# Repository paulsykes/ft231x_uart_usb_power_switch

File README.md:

FT231X UART USB Power Switch
================================

FT231X USB to serial UART with integrated current limited USB power switch.

It also allows you to switch on and off power to a USB powered device. This is super useful if you are debugging the serial output of a device during hard reset conditions and wish to automate the reset process, even more so if the device you are trying to monitor is connected to a remote computer.

- USB to UART
- USB power output switched by FT231X CBUS0 pin
- Active low, over current status readable by FT231X CBUS3 pin (500 mA)
- Solder jumper to default USB power to on or off
- USB data lines are connected to the FT231X, they are *NOT* passed through to the power switchable USB Type A port. 

Documentation
-------------
Compiled documentation can be read [here](https://paulsykes.me/ft231x_uart_usb_power_switch). Documentation source and build instructions [here](docsrc).

Manufacturing & Releases
------------------------
Fabrication outputs (Gerbers/BoM/etc..) are automatically generated for each release, the latest of which can be found [here](https://github.com/paulsykes/ft231x_uart_usb_power_switch/releases/latest). Instructions for locally generating manufacturing outputs can be found [here](hardware/kicad/ft231x_uart_usb_power_switch).

License Information
-------------------
All contents of this repository are released under [Creative Commons Share-alike 4.0](http://creativecommons.org/licenses/by-sa/4.0/).

Author
------
Paul Sykes, [My Blog](https://paulsykes.me)

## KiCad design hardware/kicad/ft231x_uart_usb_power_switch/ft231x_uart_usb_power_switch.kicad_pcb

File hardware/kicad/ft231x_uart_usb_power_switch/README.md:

Fabrication
===========
The fabrication outputs (Gebers/BoM/etc..) for this project are built using
[KiBot](https://github.com/INTI-CMNB/KiBot). The outputs are automatically generated for each release, the latest of which can be found [here](https://github.com/paulsykes/ft231x_breakout_usb_power_switch/releases/latest).This document will cover generating manufacturing outputs locally.

Build Environment
-----------------
KiBot installation on Ubuntu/Debian. For other OS, please see [KiBot Documentation](https://github.com/skorokithakis/KiBot/blob/master/README.md).
```
$ wget https://github.com/INTI-CMNB/KiBot/releases/download/v0.10.0-4/kibot_0.10.0-4_all.deb
$ sudo apt install ./kibot_0.10.0-4_all.deb
```
KiBot installation on Ubuntu/Debian.
```
$ wget https://github.com/INTI-CMNB/KiAuto/releases/download/v1.5.8/kiauto_1.5.8-1_all.deb
$ sudo apt install ./kiauto_1.5.8-1_all.deb
```
InteractiveHtmlBom installation Ubuntu/Debian.
```
$ wget https://github.com/INTI-CMNB/InteractiveHtmlBom/releases/download/v2.3.4-2/interactivehtmlbom.inti-cmnb_2.3.4-2_all.deb
$ sudo apt install ./interactivehtmlbom.inti-cmnb_2.3.4-2_all.deb
```

Generate Fabrication Outputs
----------------------------
Fabrication outputs will generated inside the [fabrication](fabrication) folder.
``` 
$ cd hardware/kicad/ft231x_breakout_usb_power_switch
$ make
```

Delete Fabrication Outputs
----------------------------
Delete all fabrication outputs.
``` 
$ make clean
```

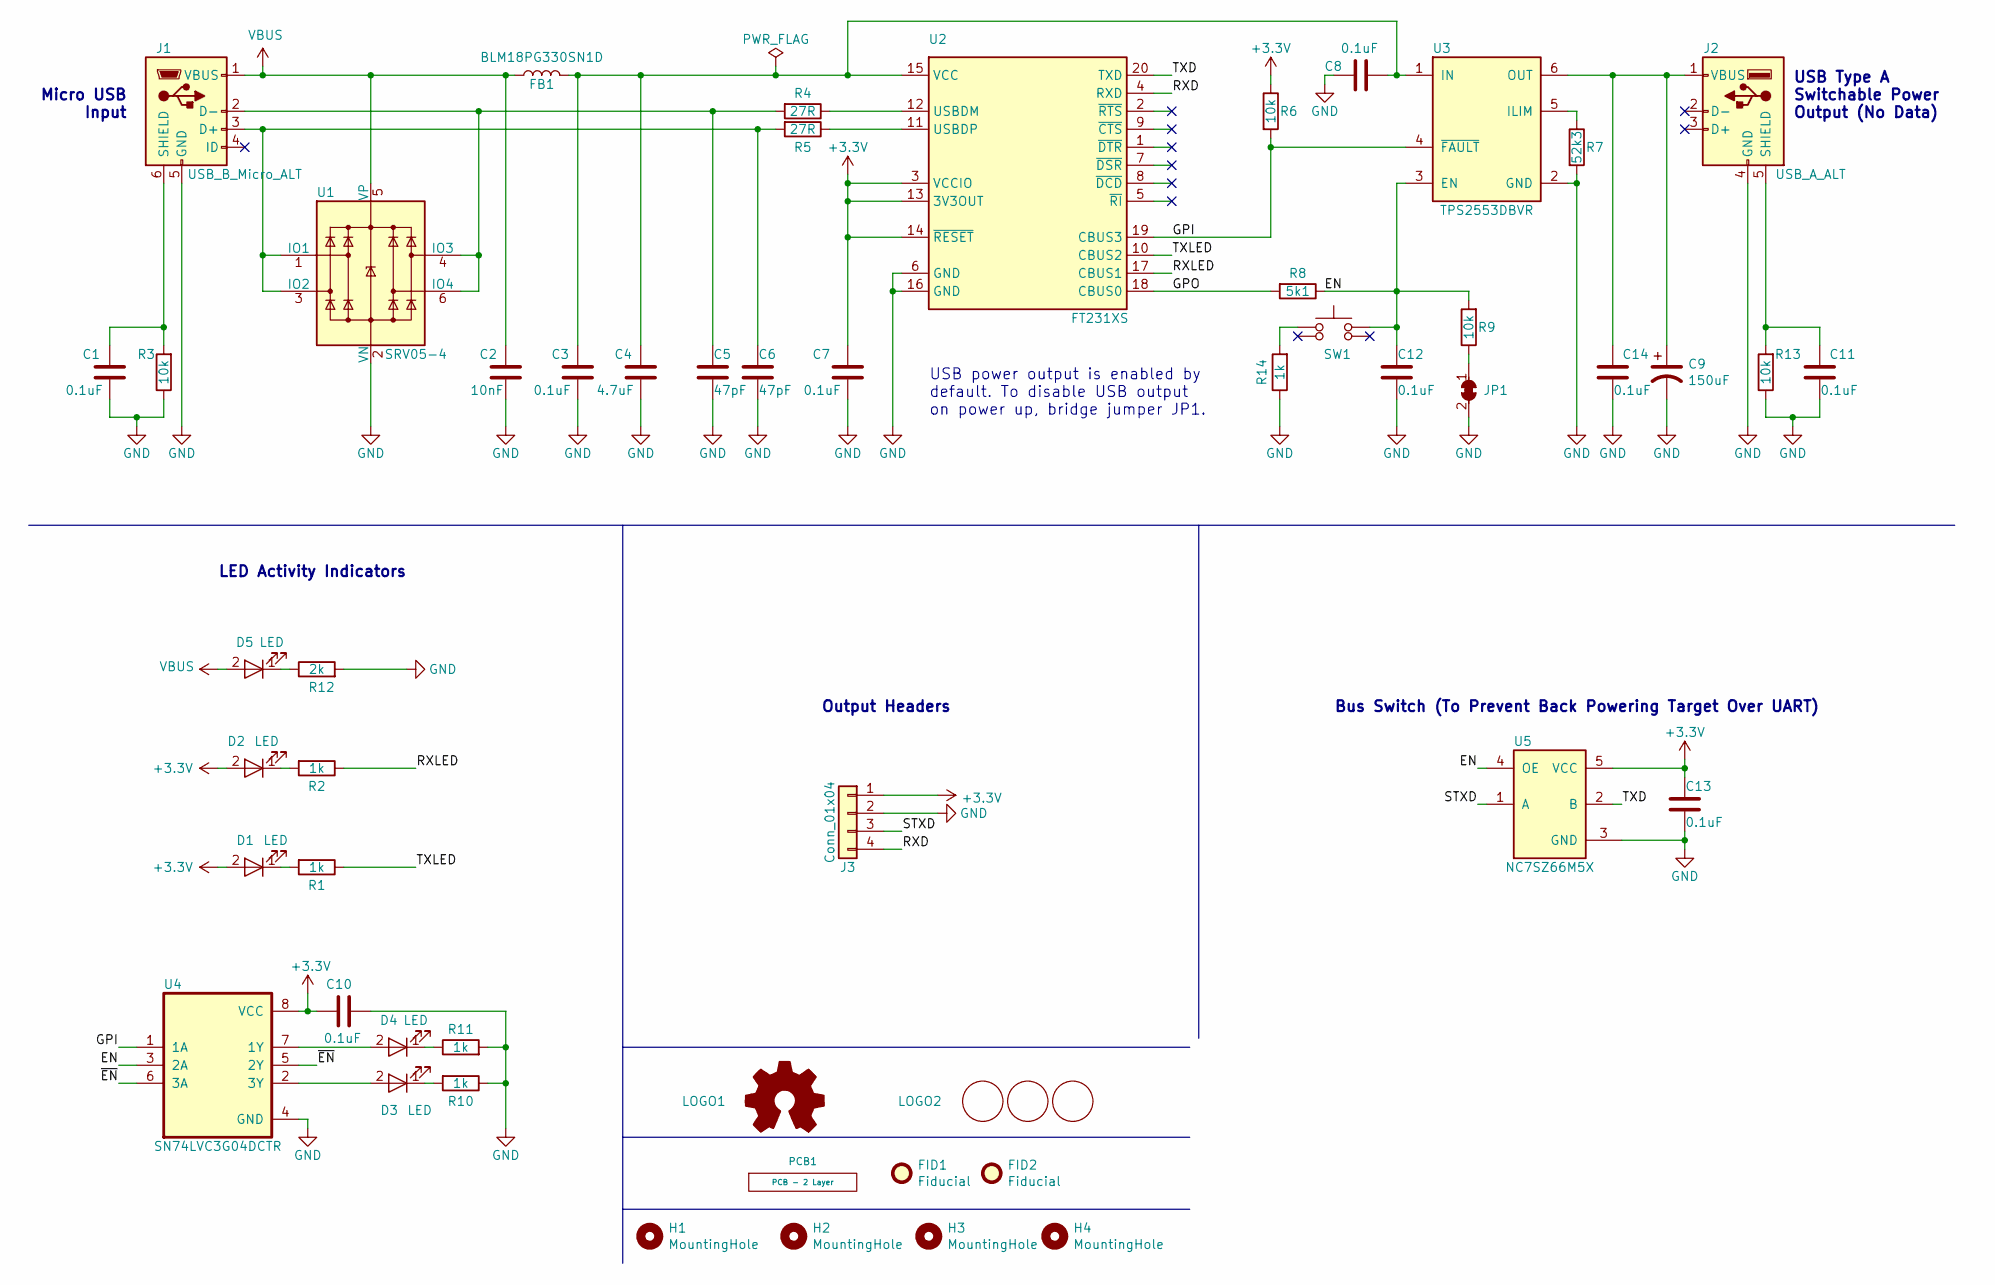
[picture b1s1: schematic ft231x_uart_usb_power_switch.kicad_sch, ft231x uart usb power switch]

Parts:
C1, C3, C7, C8, C10, C11, C12, C13, C14: 0.1uF; C_0603; mouser# 603-CC603KRX7R9BB104; LCSC# C14663
C2: 10nF; C_0603; mouser# 603-CC603KRX7R9BB103; LCSC# C100042
C4: 4.7uF; C_0603; mouser# 603-CC603KRX5R6BB475; LCSC# C109456
C5, C6: 47pF; C_0603; mouser# 603-CC603JRNPO9BN470; LCSC# C105622
C9: 150uF; EIA-3528-12_Kemet-T_DENSITY_MEDIUM; mouser# 80-T520B157M006ATE25; LCSC# C156458
D1, D2, D3, D4, D5: LED; LED_0603_1608Metric; mouser# 638-19217GHCYR1S23T; LCSC# C72043
FB1: BLM18PG330SN1D; FB_0603; mouser# 81-BLM18PG330SN1D; LCSC# C88984
FID1, FID2: Fiducial; Fiducial_1mm_Mask2mm
H1, H3: MountingHole; MountingHole_2.6mm_annular
H2, H4: MountingHole; MountingHole_2.6mm_nocrtyd
J1: USB_B_Micro_ALT; AMPHENOL_10118194-0001LF; mouser# 649-10118194-0001LF; LCSC# C132563
J2: USB_A_ALT; TE_292303-1; mouser# 571-292303-1; LCSC# C86461
J3: Conn_01x04; PinHeader_1x04_P2.54mm_Vertical_Arduino; LCSC# C124378
JP1: SolderJumper_2_Bridged_Alt; SolderJumper-2_P1.3mm_Un-Bridged_RoundedPad1.0x1.5mm
LOGO1: Logo_Open_Hardware_Small; OSHW-Logo2_7.3x6mm_SilkScreen
LOGO2: Logo_CC_BY_SA; cc_by_sa
PCB1: PCB - 2 Layer
R1, R2, R10, R11, R14: 1k; R_0603; mouser# 603-RC0603JR-071KL; LCSC# C14676
R3, R6, R9, R13: 10k; R_0603; mouser# 603-RC0603JR-0710KL; LCSC# C99198
R4, R5: 27R; R_0603; mouser# 603-RC0603FR-0727RL; LCSC# C137753
R7: 52k3; R_0603; mouser# 603-RC0603FR-0752K3L; LCSC# C185323
R8: 5k1; R_0603; mouser# 603-RC0603JR-075K1L; LCSC# C14677
R12: 2k; R_0603; mouser# 603-RC0603JR-072KL; LCSC# C105581
SW1: PTS810SJK250SMTRLFS; PTS810SJK250SMTRLFS-TACT4.2MM; mouser# 611-PTS810SJK250SMTR; LCSC# C221896
U1: SRV05-4; SOT-23-6; LCSC# C558418
U2: FT231XS; SSOP-20_3.9x8.7mm_P0.635mm; mouser# 895-FT231XS-R; LCSC# C132160
U3: TPS2553DBVR; VSON-10-1EP_3x3mm_P0.5mm_EP1.65x2.4mm_ThermalVias; mouser# 595-TPS2553DBVR; LCSC# C55266
U4: SN74LVC3G04DCTR; SSOP-8_2.95x2.8mm_P0.65mm; mouser# 595-SN74LVC3G04DCTR; LCSC# C139324
U5: NC7SZ66M5X; SOT-23-5; mouser# 512-NC7SZ66M5X; LCSC# C232791

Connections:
+3V3: C7.1, C10.1, C13.1, D1.2 (A), D2.2 (A), J3.1, R6.1, U2.3 (VCCIO), U2.13 (3V3OUT), U2.14 (~RESET), U4.8 (VCC), U5.5 (VCC)
/EN: C12.1, R8.1, R9.2, SW1.3 (B), U3.3 (EN), U4.3 (2A), U5.4 (OE)
/GPI: R6.2, U2.19 (CBUS3), U3.4 (~FAULT), U4.1 (1A)
/GPO: R8.2, U2.18 (CBUS0)
/RXD: J3.4, U2.4 (RXD)
/RXLED: R2.1, U2.17 (CBUS1)
/STXD: J3.3, U5.1 (A)
/TXD: U2.20 (TXD), U5.2 (B)
/TXLED: R1.1, U2.10 (CBUS2)
/~EN: U4.5 (2Y), U4.6 (3A)
GND: C1.2, C2.2, C3.2, C4.2, C5.2, C6.2, C7.2, C8.1, C9.2, C10.2, C11.2, C12.2, C13.2, C14.2, J1.5 (GND), J2.4 (GND), J3.2, JP1.2 (B), R3.1, R7.2, R10.1, R11.2, R12.2, R13.1, R14.1, U1.2 (VN), U2.6 (GND), U2.16 (GND), U3.2 (GND), U4.4 (GND), U5.3 (GND)
unnamed: C1.1, J1.6 (SHIELD), R3.2
unnamed: C3.1, C4.1, C8.2, FB1.2, U2.15 (VCC), U3.1 (IN)
unnamed: C5.1, J1.2 (D-), R4.2, U1.4 (IO3), U1.6 (IO4)
unnamed: C6.1, J1.3 (D+), R5.2, U1.1 (IO1), U1.3 (IO2)
unnamed: C11.1, J2.5 (SHIELD), R13.2
unnamed: C9.1, C14.1, J2.1 (VBUS), U3.6 (OUT)
unnamed: D1.1 (K), R1.2
unnamed: D2.1 (K), R2.2
unnamed: D3.1 (K), R10.2
unnamed: D3.2 (A), U4.2 (3Y)
unnamed: D4.1 (K), R11.1
unnamed: D4.2 (A), U4.7 (1Y)
unnamed: D5.1 (K), R12.1
unnamed: JP1.1 (A), R9.1
unnamed: R4.1, U2.12 (USBDM)
unnamed: R5.1, U2.11 (USBDP)
unnamed: R7.1, U3.5 (ILIM)
unnamed: R14.2, SW1.1 (A)
VBUS: C2.1, D5.2 (A), FB1.1, J1.1 (VBUS), U1.5 (VP)

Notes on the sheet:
USB power output is enabled by default. To disable USB output on power up, bridge jumper JP1.
Output Headers
Micro USB Input
Bus Switch (To Prevent Back Powering Target Over UART)
USB Type A Switchable Power Output (No Data)
LED Activity Indicators

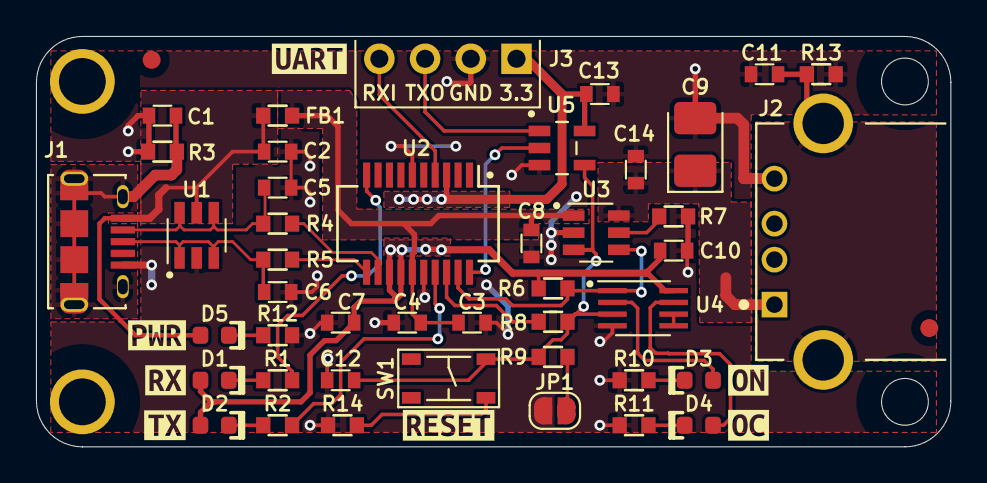
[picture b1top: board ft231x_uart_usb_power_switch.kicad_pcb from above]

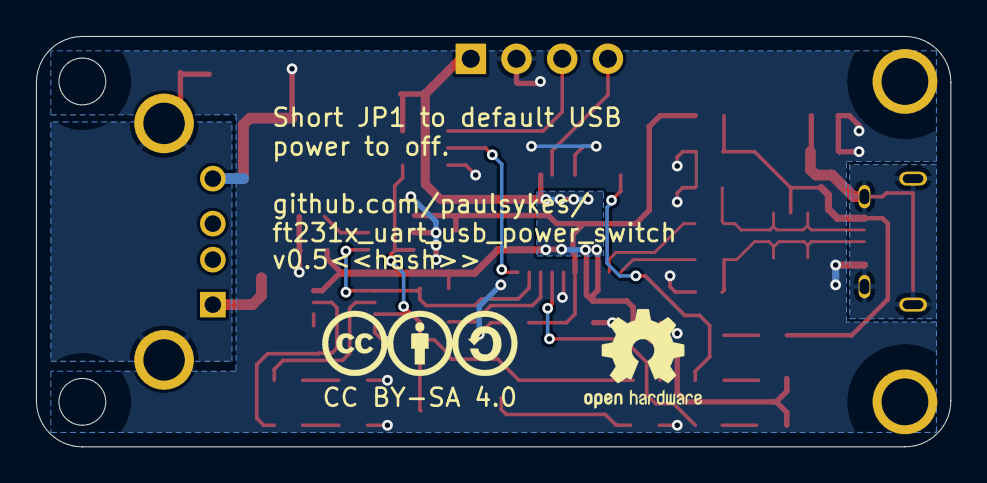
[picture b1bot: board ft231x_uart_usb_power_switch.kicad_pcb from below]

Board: 2 copper layers, 50.8 x 22.8 mm, 59 parts (2 on the bottom side), 30 nets.

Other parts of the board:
kibuzzard-6210B9B1: G***; kibuzzard-6210B9B1
kibuzzard-6210BA4A: G***; kibuzzard-6210BA4A
kibuzzard-6210BA5D: G***; kibuzzard-6210BA5D
kibuzzard-6210BA32: G***; kibuzzard-6210BA32
kibuzzard-6210BA40: G***; kibuzzard-6210BA40
kibuzzard-6210BA51: G***; kibuzzard-6210BA51
kibuzzard-6210BA58: G***; kibuzzard-6210BA58

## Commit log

2021-02-08 initial import
2021-02-08 add gitignore
2021-02-08 remove backup files
2021-02-08 remove more backup files
2021-02-08 add freecad to git ignore
2021-02-08 remove unused 3d models
2021-02-08 more local 3d models
2021-02-09 add usb to led silkscreen
2021-02-09 kibot yaml file
2021-02-09 test jobs
2021-02-09 move workflows to correct folder
2021-02-09 correct paths
2021-02-09 typo fix
2021-02-09 fix paths in gitignore
2021-02-09 rename typo
2021-02-09 CI test
2021-02-09 test workflow
    test workflow
2021-02-09 master to main
2021-02-09 remove test action blank
2021-02-09 tidy up kibot library warnings
2021-02-09 change output directory
2021-02-09 add drc github action
2021-02-09 fix typo
2021-02-09 test
2021-02-09 test2
2021-02-09 test3
2021-02-09 test4
2021-02-09 test5
2021-02-09 test6
2021-02-09 test7
2021-02-09 test8
2021-02-09 test9
2021-02-09 test10
2021-02-09 test11
2021-02-09 test12
2021-02-09 test13
2021-02-09 update makefile
2021-02-09 cleanup cache file
2021-02-09 more to ignore
2021-02-09 initial gerber test
2021-02-09 trigger action if kibot config file updated
2021-02-14 add no docs folder
2021-02-14 initial documentation structure
2021-02-14 Read the Docs theme
2021-02-15 making a start on the docs
2021-02-16 use sphinx-tabs for os
2021-02-16 inital docsrc readme
2021-02-16 sphinx documentation requirements
2021-02-16 kibot documentation
2021-02-16 fabrication directory
2021-02-16 2D renders
2021-02-16 declare destination in makefile only
2021-02-16 add JLCPCB gerber generation
2021-02-17 PCB vendor configs
2021-02-17 add layout version number
2021-02-17 ignore more kibot files
2021-02-17 new workflow
2021-02-17 make clean delete kibot log file
2021-02-17 use directory name in makefile
2021-02-17 Add JLCPCB with stencil config
2021-02-17 jlc style bom and position file generation
2021-02-18 Bom fields test
2021-02-18 change footprint FT231XS to fix lcsc rotation filter
2021-02-18 remove unused footprint
2021-02-18 Add substitute field
2021-02-18 Add value to kibot kibom grouping
2021-02-18 bom fields for 0.1uF caps
2021-02-18 10nF cap BOM fields
2021-02-18 BOM fields 47 pF cap
2021-02-18 4.7 uF BOM fields
2021-02-18 150 uF cap bom fields
2021-02-18 LED bom fields
2021-02-19 bom fields for more parts
2021-02-19 update more fields bom
2021-02-19 Update Bom fields connectors
2021-02-21 Tidy up footprints and BoM fields
2021-02-24 test release
2021-02-24 tag in workflow
2021-02-24 fix indentation issue workflow
2021-02-24 commit release
2021-02-24 fix type
2021-02-24 run on tag
2021-02-24 test test
2021-02-24 test more github actions
2021-02-24 test more github actions1
2021-02-24 more github action test
2021-02-24 github more test3
2021-02-24 test zip 1
2021-02-24 zipagain
2021-02-24 zipagain2
2021-02-24 conditional reference
2021-02-26 generate 3d model
2021-02-26 exclude mounting holes
2021-02-26 remove solder jumper from bom
2021-02-26 early partsbox bom support
2021-02-27 remove F from filter as this was filtering out ferrite beads
2021-02-27 Add details BoM details for ferrite bead
2021-02-27 pad version number
2021-02-27 try to make actions run again
2021-02-27 why not running
2021-03-01 reset switch initial
2021-03-01 fix unconnected ground
2021-03-01 test move tags
2021-03-01 move tags action again
2021-03-01 add optional pull down to enable
2021-03-02 Reset switch and bus switches routed
2021-03-03 increase pad sizes for easier hand assembly
2021-03-03 remove tag filter
2021-03-03 Fix reset when FT231X is drivng power switch OE
2021-03-03 KiBuzzard labels
2021-03-09 use github workflow to add hash to silkscreen
2021-03-09 install git cli
2021-03-16 add fiducial symbol and component
2021-03-16 Add two fiducials
2021-03-23 update resistor values in enable line
2021-03-23 remove breakout headers and simplify
2021-03-24 change to larger tactile switch
2021-03-24 use buffer for on indicator
2021-03-25 0.3-rc1 removed breakout headers
2021-03-25 0.3 rc2 fix zone fills
2021-03-25 Add open hardware logos
2021-03-25 add missing 3d model
2021-03-25 update 3d model in library
2021-03-25 disable 3d step file generation
2021-03-25 add dot
2021-03-25 re-add silk buzzard labels
2021-03-26 rename project breakout to uart
2021-03-26 rename kibot file breakout to uart
2021-03-26 update documentation breakout to uart
2021-03-26 remove fiducials from bom
2021-03-26 add back sym-lib-table
2021-03-26 install kikit
2021-03-26 add pip3
2021-03-26 add kikit stencil to workflow
2021-03-26 install zip for kikit
2021-10-14 Update Design Based On Feedback
    * Add Power LED
    * Add 3.3V to header
    * Swap RX and TX Label (This was labelled from USB perspective, now labelled from UART perspective)
2022-02-07 Update source files to kicad 6
2022-02-07 Set kibot to dev_k6 container
2022-02-07 Update DRC to dev_k6
2022-02-07 Move pcb fab to dev_k6
2022-02-19 Increase size of kibuzzard labels
2022-02-27 Open up solder paste holes for mechanical pins Micro USB

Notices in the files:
parts and their libraries:
CC BY-SA 4.0
